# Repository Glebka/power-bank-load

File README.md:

# PowerBankLoad

This device prevents my power bank from sleep when I am trying to power my DIY devices that draw less than 150 mA of power.

It is inspired by the blog post [Battery Pack Load](https://dorkbotpdx.org/blog/paul/battery_pack_load/) by Paul.

I changed a schematic, so it uses 555 timer to generate pulses instead of two bipolar transistors.
Well,  you may say that it is an overkill, however, I feel more comfortable with timer than with two transistors I need to adjust.
As a bonus, device supports adjusting pulse width and frequency.

## 3D View

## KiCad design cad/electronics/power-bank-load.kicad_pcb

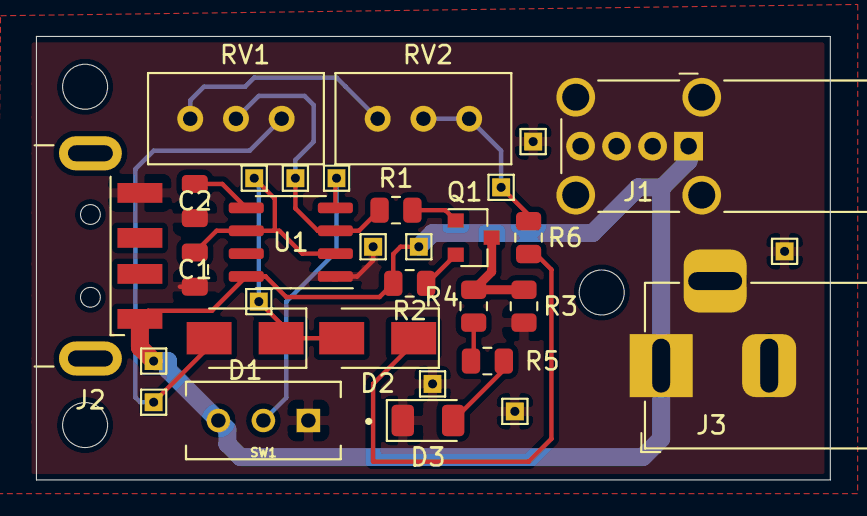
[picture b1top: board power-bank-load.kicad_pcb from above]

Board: 2 copper layers, 44.1 x 24.6 mm, 19 parts (0 on the bottom side), 15 nets.

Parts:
C1, C2: 1uF; C_0805_2012Metric
D1, D2: 1N401; D_SMA
D3: LED; LED_1206_3216Metric
J1: USB_A; USB_A_Wuerth_614004134726_Horizontal
J2: USB_A; USB_A_CNCTech_1001-011-01101_Horizontal
J3: Barrel_Jack_Switch; BarrelJack_Horizontal
Q1: MMBT2222A; SOT-23
R1, R5: 1k; R_0805_2012Metric
R2: 22; R_0805_2012Metric
R3, R4: 0; R_0805_2012Metric
R6: 680k; R_0805_2012Metric
RV1: 100k; Potentiometer_Bourns_3296W_Vertical
RV2: 1M; Potentiometer_Bourns_3296W_Vertical
SW1: SW_SPDT; SW_OS102011MS2QN1
U1: NE555D; SOIC-8_3.9x4.9mm_P1.27mm

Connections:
+5V: J1.1, J2.1, J3.1, R2.1, SW1.3, U1.8
GND: C1.2, C2.2, D3.1, J1.4, J2.4, J3.2, J3.3, R3.2, SW1.1, U1.1
unnamed: C1.1, D1.1, D2.2, U1.2, U1.6
unnamed: C2.1, U1.5
unnamed: D1.2, RV1.3
unnamed: D2.1, R6.1
unnamed: D3.2, R5.2
unnamed: Q1.1, R1.1
unnamed: Q1.2, R2.2
unnamed: Q1.3, R3.1, R4.1
unnamed: R1.2, RV1.2, U1.3
unnamed: R4.2, R5.1
unnamed: R6.2, RV2.2, RV2.3
unnamed: RV1.1, RV2.1
unnamed: SW1.2, U1.4

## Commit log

2022-07-17 Fix images
